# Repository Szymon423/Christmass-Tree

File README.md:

<div align="center">

# Christmass Tree

</div>

This project is about creating chritmass tree made of PCB with bunch of LEDs. There is not much functionality. I just want it to look pretty.

If You have spare Arduino Uno - You can have Your own little christmass tree.

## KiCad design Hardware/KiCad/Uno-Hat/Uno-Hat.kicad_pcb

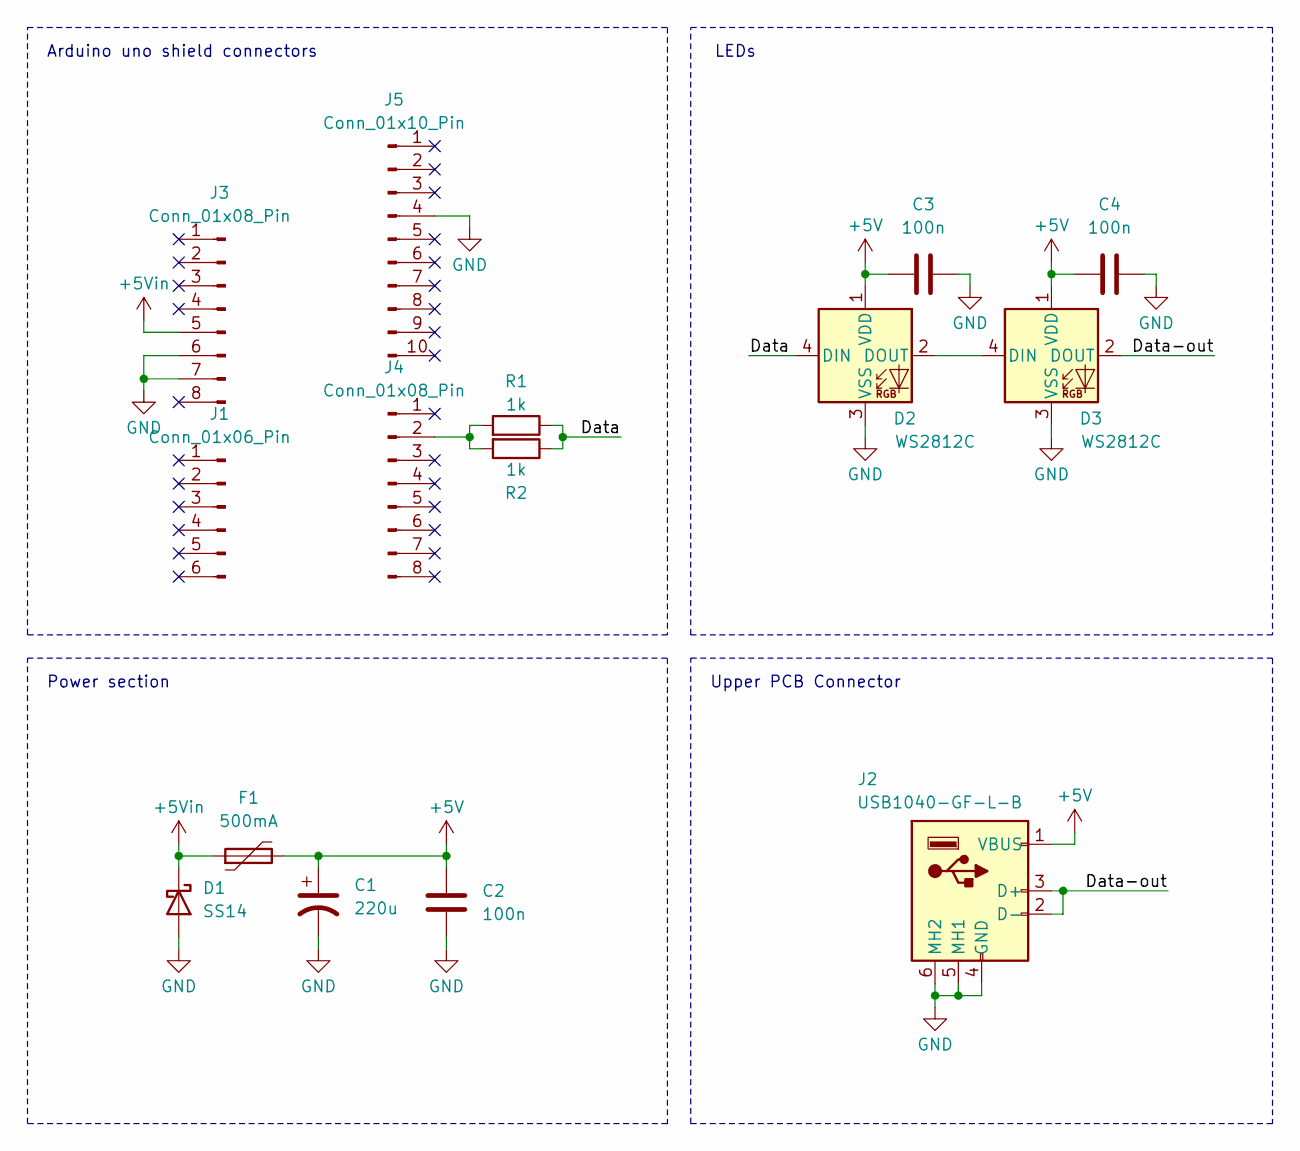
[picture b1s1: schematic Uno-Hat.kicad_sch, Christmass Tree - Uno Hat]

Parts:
C1: 220u; CP_Elec_6.3x7.7
C2, C3, C4: 100n; C_0805_2012Metric
D1: SS14; D_SMA
D2, D3: WS2812C; LED_WS2812B_PLCC4_5.0x5.0mm_P3.2mm
F1: 500mA; Fuse_1206_3216Metric
J1: Conn_01x06_Pin; PinHeader_1x06_P2.54mm_Vertical
J2: USB1040-GF-L-B; USB1040-GF-L-B-4; Manufacturer_Part_Number USB1040-GF-L-B
J3, J4: Conn_01x08_Pin; PinHeader_1x08_P2.54mm_Vertical
J5: Conn_01x10_Pin; PinHeader_1x10_P2.54mm_Vertical
R1, R2: 1k; R_0805_2012Metric

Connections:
+5V: C1.1, C2.1, C3.1, C4.1, D2.1 (VDD), D3.1 (VDD), F1.2, J2.1 (VBUS)
+5Vin: D1.1 (K), F1.1, J3.5
/Data: D2.4 (DIN), R1.1, R2.1
/Data-out: D3.2 (DOUT), J2.2 (D-), J2.3 (D+)
GND: C1.2, C2.2, C3.2, C4.2, D1.2 (A), D2.3 (VSS), D3.3 (VSS), J2.4 (GND), J2.5 (MH1), J2.6 (MH2), J3.6, J3.7, J5.4
unnamed: D2.2 (DOUT), D3.4 (DIN)
unnamed: J4.2, R1.2, R2.2

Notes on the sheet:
Power section
Arduino uno shield connectors
LEDs
Upper PCB Connector

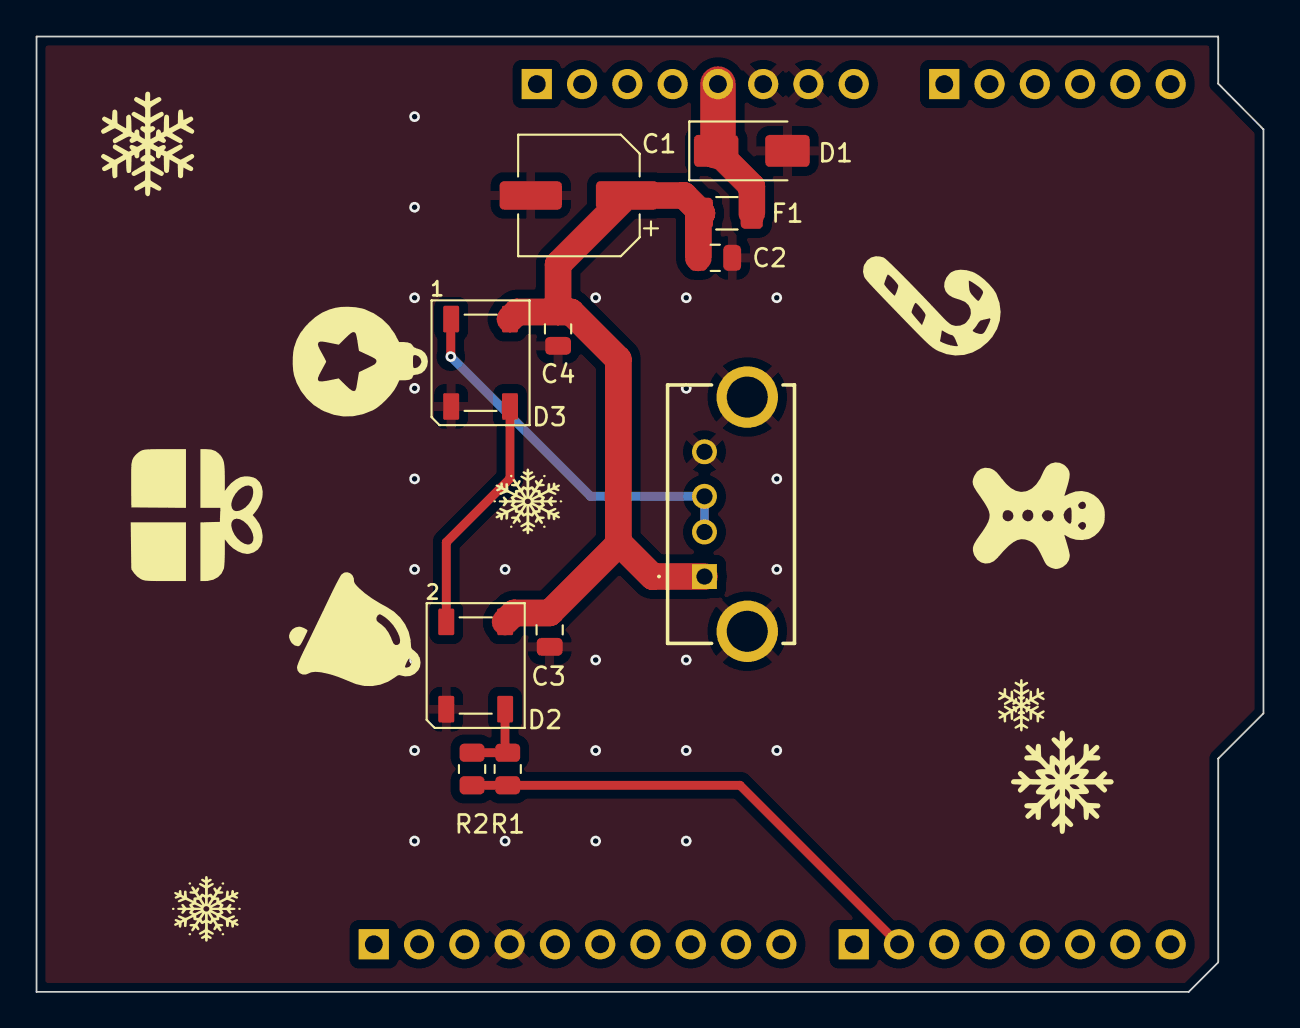
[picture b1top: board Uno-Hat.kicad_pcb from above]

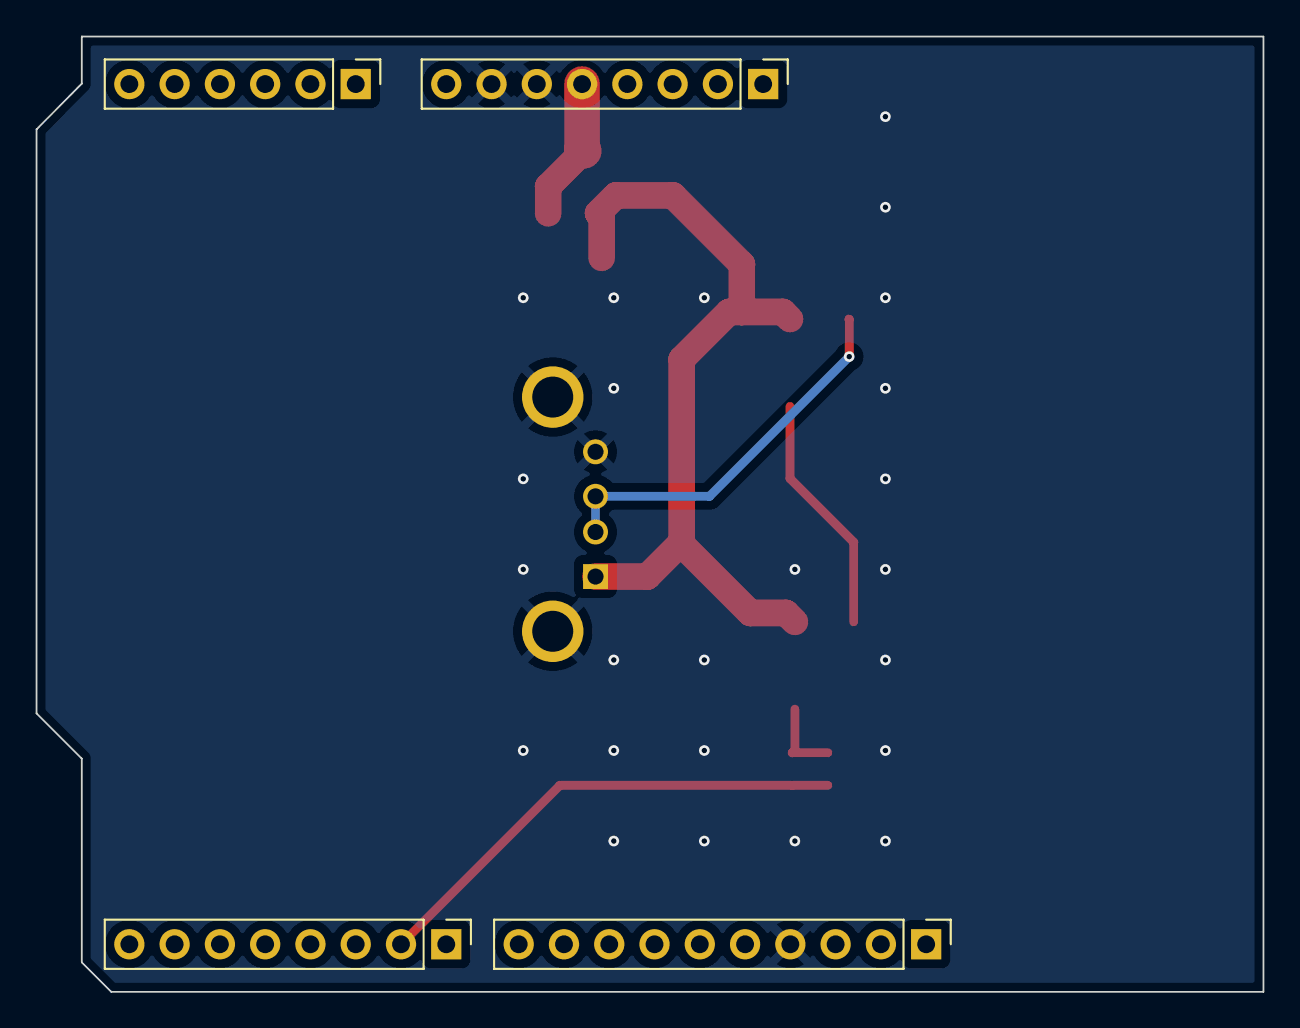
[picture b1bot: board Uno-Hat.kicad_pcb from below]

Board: 2 copper layers, 68.8 x 53.6 mm, 15 parts (4 on the bottom side), 7 nets.

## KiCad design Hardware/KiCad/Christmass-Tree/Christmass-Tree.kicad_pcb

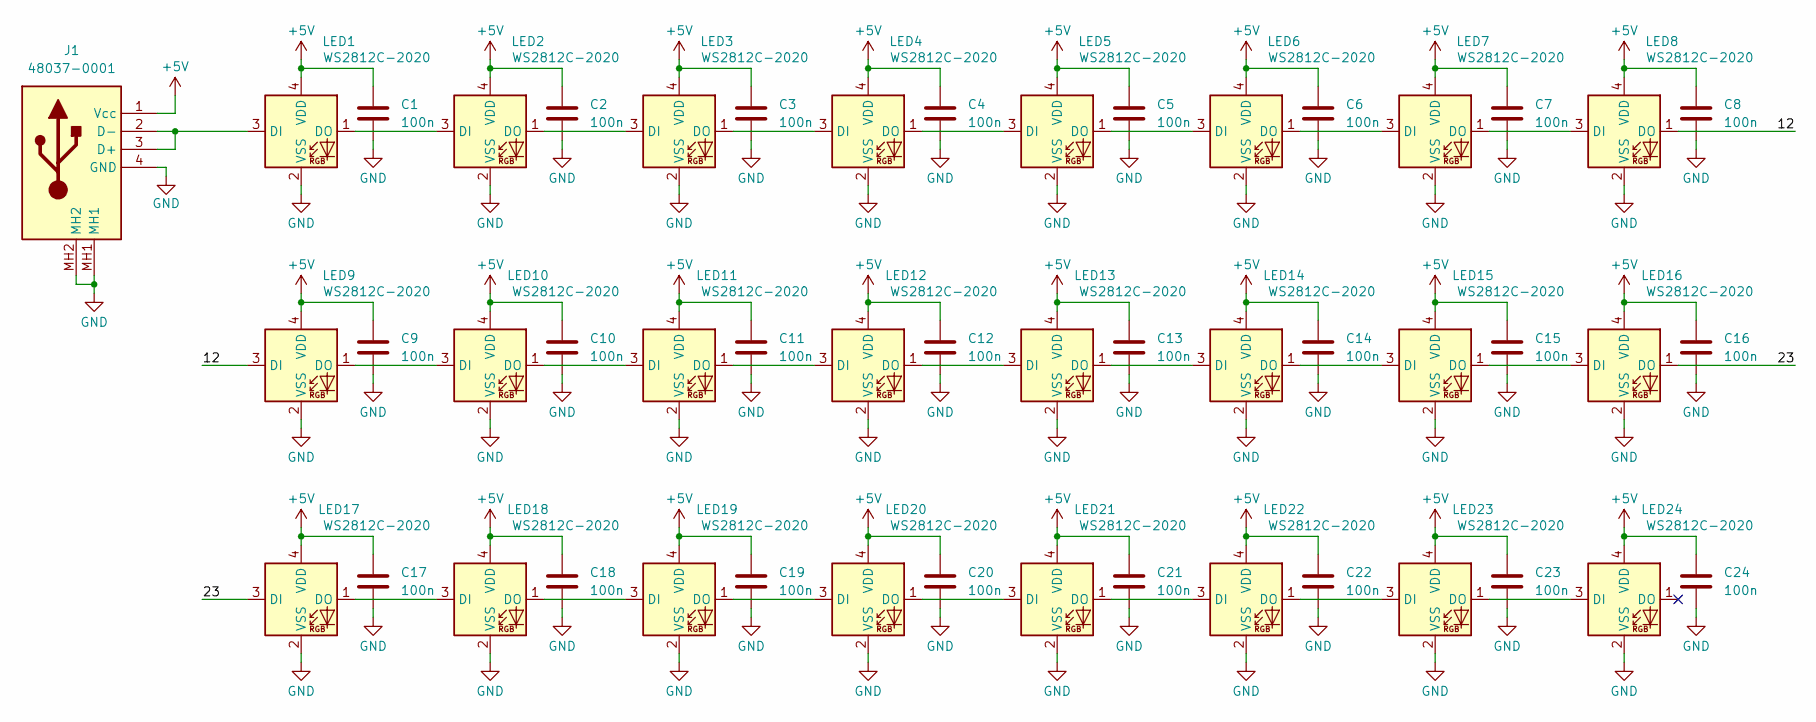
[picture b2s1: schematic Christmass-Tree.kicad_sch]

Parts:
C1, C2, C3, C4, C5, C6, C7, C8, C9, C10, C11, C12, C13, C14, C15, C16, C17, C18, C19, C20, C21, C22, C23, C24: 100n; C_0603_1608Metric
J1: 48037-0001; 480370001; Manufacturer_Part_Number 48037-0001
LED1, LED2, LED3, LED4, LED5, LED6, LED7, LED8, LED9, LED10, LED11, LED12, LED13, LED14, LED15, LED16, LED17, LED18, LED19, LED20, LED21, LED22, LED23, LED24: WS2812C-2020; WS2812C2020; Manufacturer_Part_Number WS2812C-2020

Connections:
+5V: C1.1, C2.1, C3.1, C4.1, C5.1, C6.1, C7.1, C8.1, C9.1, C10.1, C11.1, C12.1, C13.1, C14.1, C15.1, C16.1, C17.1, C18.1, C19.1, C20.1, C21.1, C22.1, C23.1, C24.1, J1.1 (Vcc), LED1.4 (VDD), LED2.4 (VDD), LED3.4 (VDD), LED4.4 (VDD), LED5.4 (VDD), LED6.4 (VDD), LED7.4 (VDD), LED8.4 (VDD), LED9.4 (VDD), LED10.4 (VDD), LED11.4 (VDD), LED12.4 (VDD), LED13.4 (VDD), LED14.4 (VDD), LED15.4 (VDD), LED16.4 (VDD), LED17.4 (VDD), LED18.4 (VDD), LED19.4 (VDD), LED20.4 (VDD), LED21.4 (VDD), LED22.4 (VDD), LED23.4 (VDD), LED24.4 (VDD)
/12: LED8.1 (DO), LED9.3 (DI)
/23: LED16.1 (DO), LED17.3 (DI)
GND: C1.2, C2.2, C3.2, C4.2, C5.2, C6.2, C7.2, C8.2, C9.2, C10.2, C11.2, C12.2, C13.2, C14.2, C15.2, C16.2, C17.2, C18.2, C19.2, C20.2, C21.2, C22.2, C23.2, C24.2, J1.4 (GND), J1.MH1, J1.MH2, LED1.2 (VSS), LED2.2 (VSS), LED3.2 (VSS), LED4.2 (VSS), LED5.2 (VSS), LED6.2 (VSS), LED7.2 (VSS), LED8.2 (VSS), LED9.2 (VSS), LED10.2 (VSS), LED11.2 (VSS), LED12.2 (VSS), LED13.2 (VSS), LED14.2 (VSS), LED15.2 (VSS), LED16.2 (VSS), LED17.2 (VSS), LED18.2 (VSS), LED19.2 (VSS), LED20.2 (VSS), LED21.2 (VSS), LED22.2 (VSS), LED23.2 (VSS), LED24.2 (VSS)
unnamed: J1.2 (D-), J1.3 (D+), LED1.3 (DI)
unnamed: LED1.1 (DO), LED2.3 (DI)
unnamed: LED2.1 (DO), LED3.3 (DI)
unnamed: LED3.1 (DO), LED4.3 (DI)
unnamed: LED4.1 (DO), LED5.3 (DI)
unnamed: LED5.1 (DO), LED6.3 (DI)
unnamed: LED6.1 (DO), LED7.3 (DI)
unnamed: LED7.1 (DO), LED8.3 (DI)
unnamed: LED9.1 (DO), LED10.3 (DI)
unnamed: LED10.1 (DO), LED11.3 (DI)
unnamed: LED11.1 (DO), LED12.3 (DI)
unnamed: LED12.1 (DO), LED13.3 (DI)
unnamed: LED13.1 (DO), LED14.3 (DI)
unnamed: LED14.1 (DO), LED15.3 (DI)
unnamed: LED15.1 (DO), LED16.3 (DI)
unnamed: LED17.1 (DO), LED18.3 (DI)
unnamed: LED18.1 (DO), LED19.3 (DI)
unnamed: LED19.1 (DO), LED20.3 (DI)
unnamed: LED20.1 (DO), LED21.3 (DI)
unnamed: LED21.1 (DO), LED22.3 (DI)
unnamed: LED22.1 (DO), LED23.3 (DI)
unnamed: LED23.1 (DO), LED24.3 (DI)

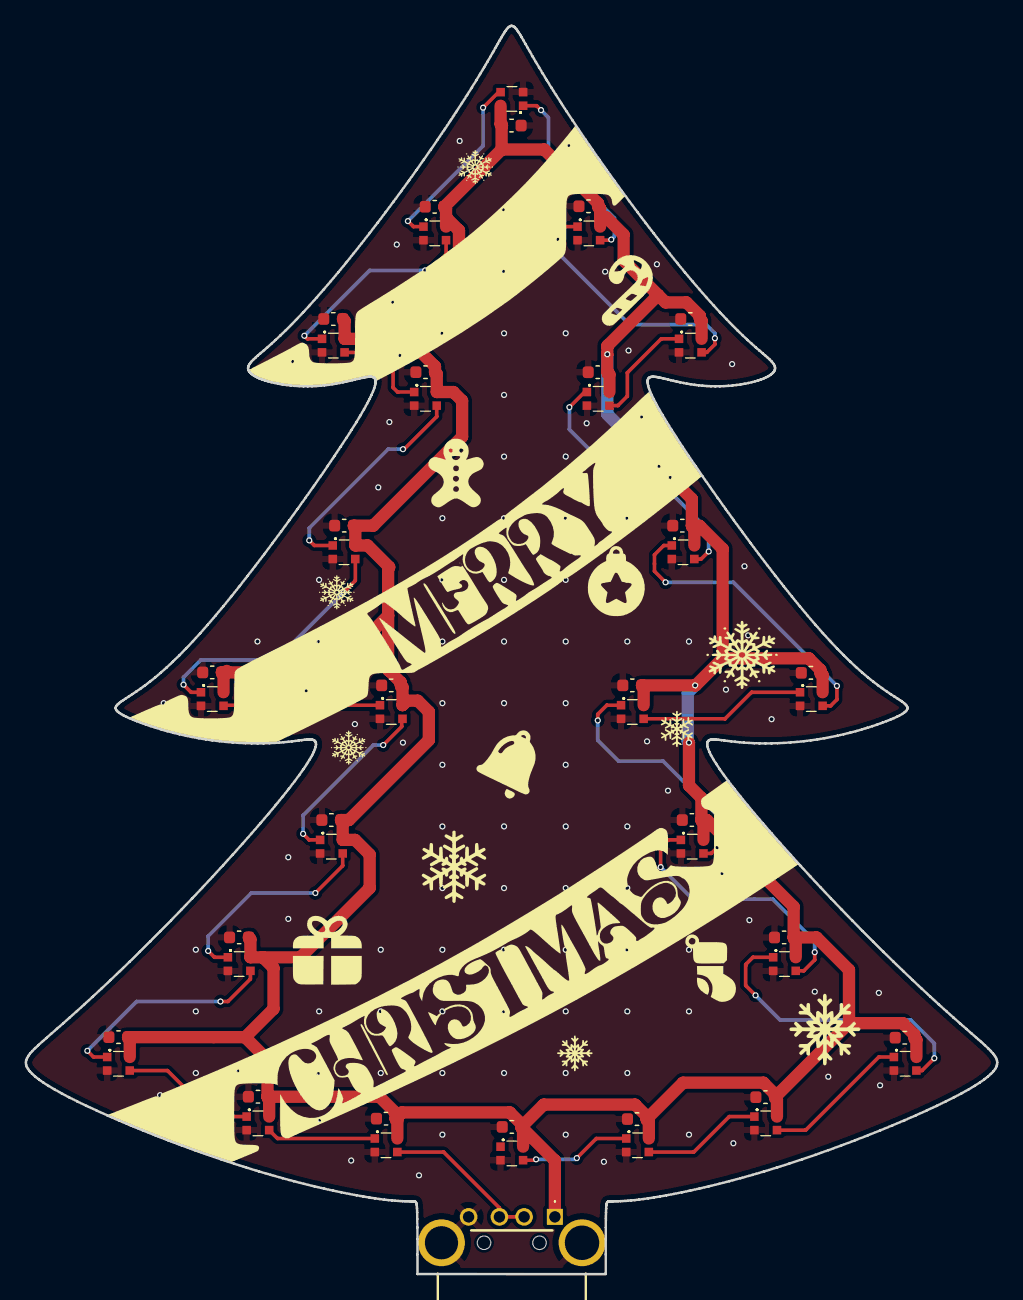
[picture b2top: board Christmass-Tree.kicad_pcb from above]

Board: 2 copper layers, 78.8 x 101.2 mm, 49 parts (0 on the bottom side), 26 nets.

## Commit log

2023-12-13 switch on interrupt with mode selector (brightness / delay)
2023-12-13 fixes and refactor
2023-12-14 some random stuff + issue on long press
2023-12-14 added 4 lightinh modes
2023-12-15 linear mode - color change not working corectly
2023-12-20 some changes in Linear color control and introduced cartesian-spherical conversion WITHOUT OFFSET!!!
2023-12-20 some trial-error
2023-12-20 I gówno, podejście jest złe - do zmiany
2023-12-21 fixed linear movement
2023-12-21 some optimisation
2024-10-27 Some refactoring of this repo
2024-10-27 fix on image
2024-11-08 New version of code just dropped
2025-11-01 Added KiCad Hardware project
